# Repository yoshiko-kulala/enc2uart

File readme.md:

# enc2uart
とある理由でエンコーダを複数arduinoで読む必要出たので作った  
[nucleo-F401RE](https://akizukidenshi.com/catalog/g/gM-07723/)でエンコーダを4つ読んでuartで送っている  

## Hou to use  
### シールド基板、エンコーダとの配線
使用時にはこのようなシールド基板を用いて動作させている  
  
基板のkicadデータ、ガーバーは[circuit/encoder](https://github.com/yoshiko-kulala/enc2uart/tree/master/circuit/encoder)にある  
回路図は最新だが、ボード図はプルアップ抵抗のないものになっている  

実際にはこのように配線すればOK  

### arduinoとの接続  
[arduino nano every](https://akizukidenshi.com/catalog/g/gM-14848/)を用いたのでserial1を使っている  
arduinoによっては[SoftwareSerial](http://www.musashinodenpa.com/arduino/ref/index.php?f=1&pos=120)でも同様に動作可能と思う  
f401側のuartとarduino側のuartを接続すればOK  
今回は下図のように接続した
| [arduino nano every](https://akizukidenshi.com/catalog/g/gM-14848/) | [nucleo-F401RE](https://akizukidenshi.com/catalog/g/gM-07723/) |
| -------- | -------- |
| 5V | 5V(arduinoから給電する場合) |
| D0 | Tx |
| GND | GND |
| D1 | Rx |

## プログラムサンプル
nucleo側プログラムは[src/encoder_test](https://github.com/yoshiko-kulala/enc2uart/tree/master/src/encoder_test)にある  
CubeIDEでそのまま書き込める(と思う)  

arduino側のプログラムは[src/read_data](https://github.com/yoshiko-kulala/enc2uart/tree/master/src/read_data)にある  
これもarduinoIDEで特に問題なく書き込めると思う  

## メモ
- データの中身
実際に送ってる値は10msごとのパルスの増減  
特に計算してないのでエンコーダの分解能によってarduino側(もしくはnucleo)で処理されたし  
- 送信時の話し  
エンコーダ1つに10bit、4つで40bitなので5byteにして送信している  
つまるところ、100msに512パルス以上来るとオーバーする  
特にその辺の処理入れてないので将来的に追加するかも  
- nucleoからのデバッグ  
nucleoとpcをusb接続して、teratermとかで115200bpsとかで読んでもらうと各エンコーダの値が出力される  
これが0ならエンコーダとnucleo間が怪しい  
これが出てたらnucleoとarduino間が怪しい

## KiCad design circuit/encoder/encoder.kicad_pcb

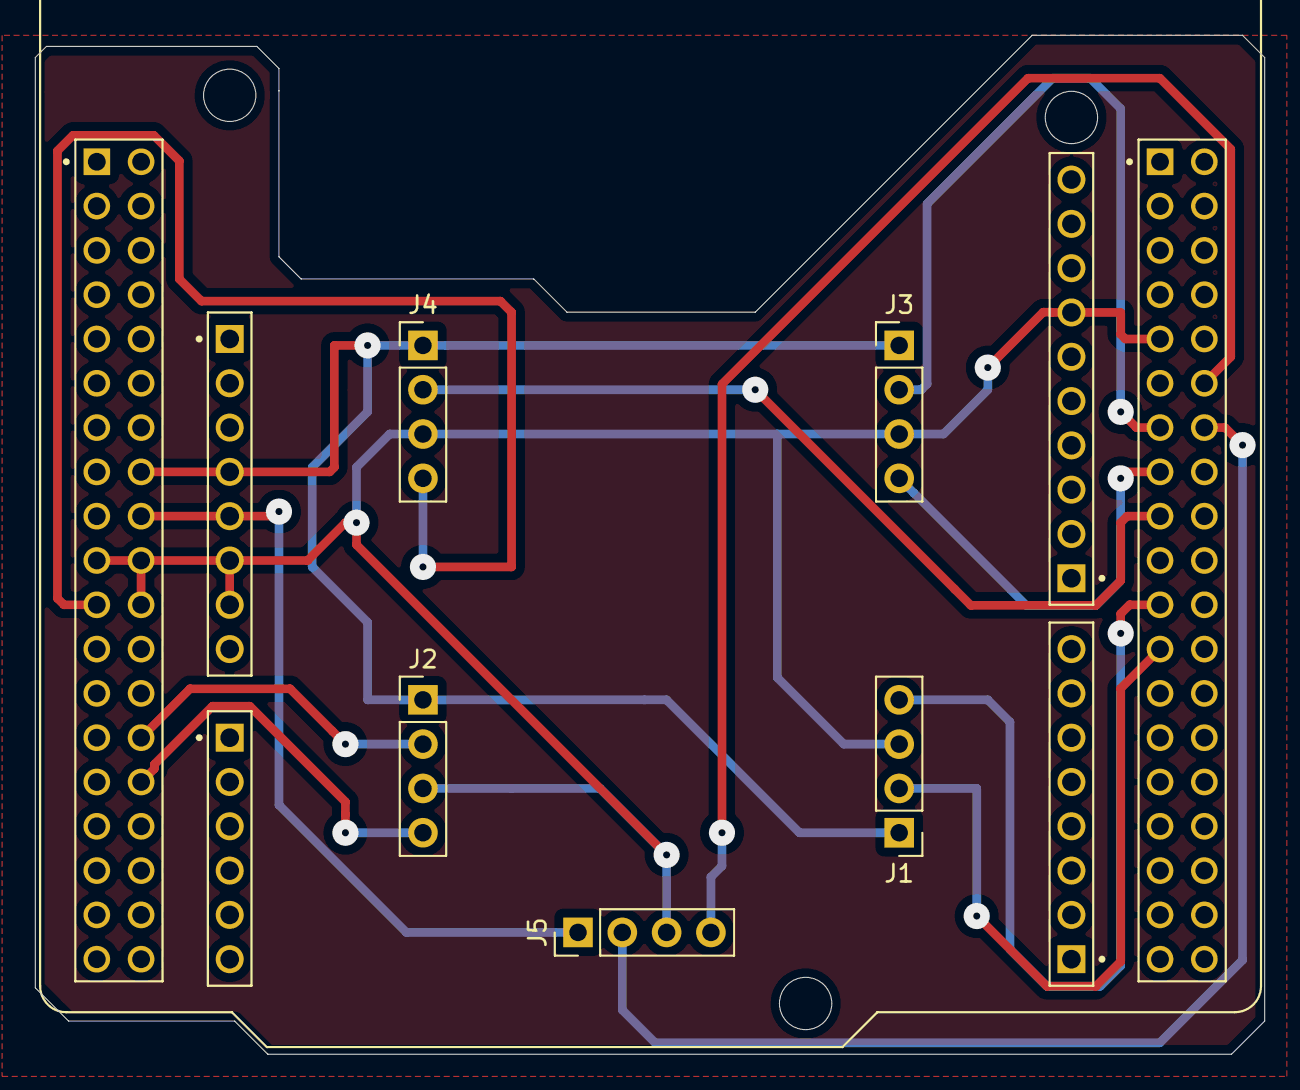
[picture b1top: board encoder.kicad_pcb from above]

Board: 2 copper layers, 70.5 x 58.4 mm, 6 parts (0 on the bottom side), 13 nets.

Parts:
A1: NUCLEO-F401RE; ST_NUCLEO-F401RE
J1: enc1; PinHeader_1x04_P2.54mm_Vertical
J2: enc2; PinHeader_1x04_P2.54mm_Vertical
J3: enc3; PinHeader_1x04_P2.54mm_Vertical
J4: enc4; PinHeader_1x04_P2.54mm_Vertical
J5: uart; PinHeader_1x04_P2.54mm_Vertical

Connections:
+3V3: A1.CN6_4, A1.CN7_16, J1.1, J2.1, J3.1, J4.1
+5V: A1.CN6_5, A1.CN7_18, J5.1
/tim1_ch1: A1.CN10_23, J1.2
/tim1_ch2: A1.CN10_21, J1.4
/tim2_ch1: A1.CN7_28, J2.2
/tim2_ch2: A1.CN7_30, J2.4
/tim3_ch1: A1.CN10_13, J3.2
/tim3_ch2: A1.CN10_15, J3.4
/tim4_ch1: A1.CN10_17, J4.2
/tim4_ch2: A1.CN7_21, J4.4
/uart6_rx: A1.CN10_12, J5.4
/uart6_tx: A1.CN10_14, J5.2
GND: A1.CN5_7, A1.CN6_6, A1.CN6_7, A1.CN7_8, A1.CN7_19, A1.CN7_20, A1.CN7_22, A1.CN10_9, A1.CN10_20, A1.CN10_32, J1.3, J2.3, J3.3, J4.3, J5.3

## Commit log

2021-06-12 add License
2021-06-12 一旦完成
2021-06-14 細かなミスの修正
